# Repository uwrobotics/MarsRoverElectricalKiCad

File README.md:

# Welcome Onboard

## New Project

### Getting started

### Active Project Lists

## Onboarding

### Getting Started

Please follow the following step to create a project from template, step by step and complete the project

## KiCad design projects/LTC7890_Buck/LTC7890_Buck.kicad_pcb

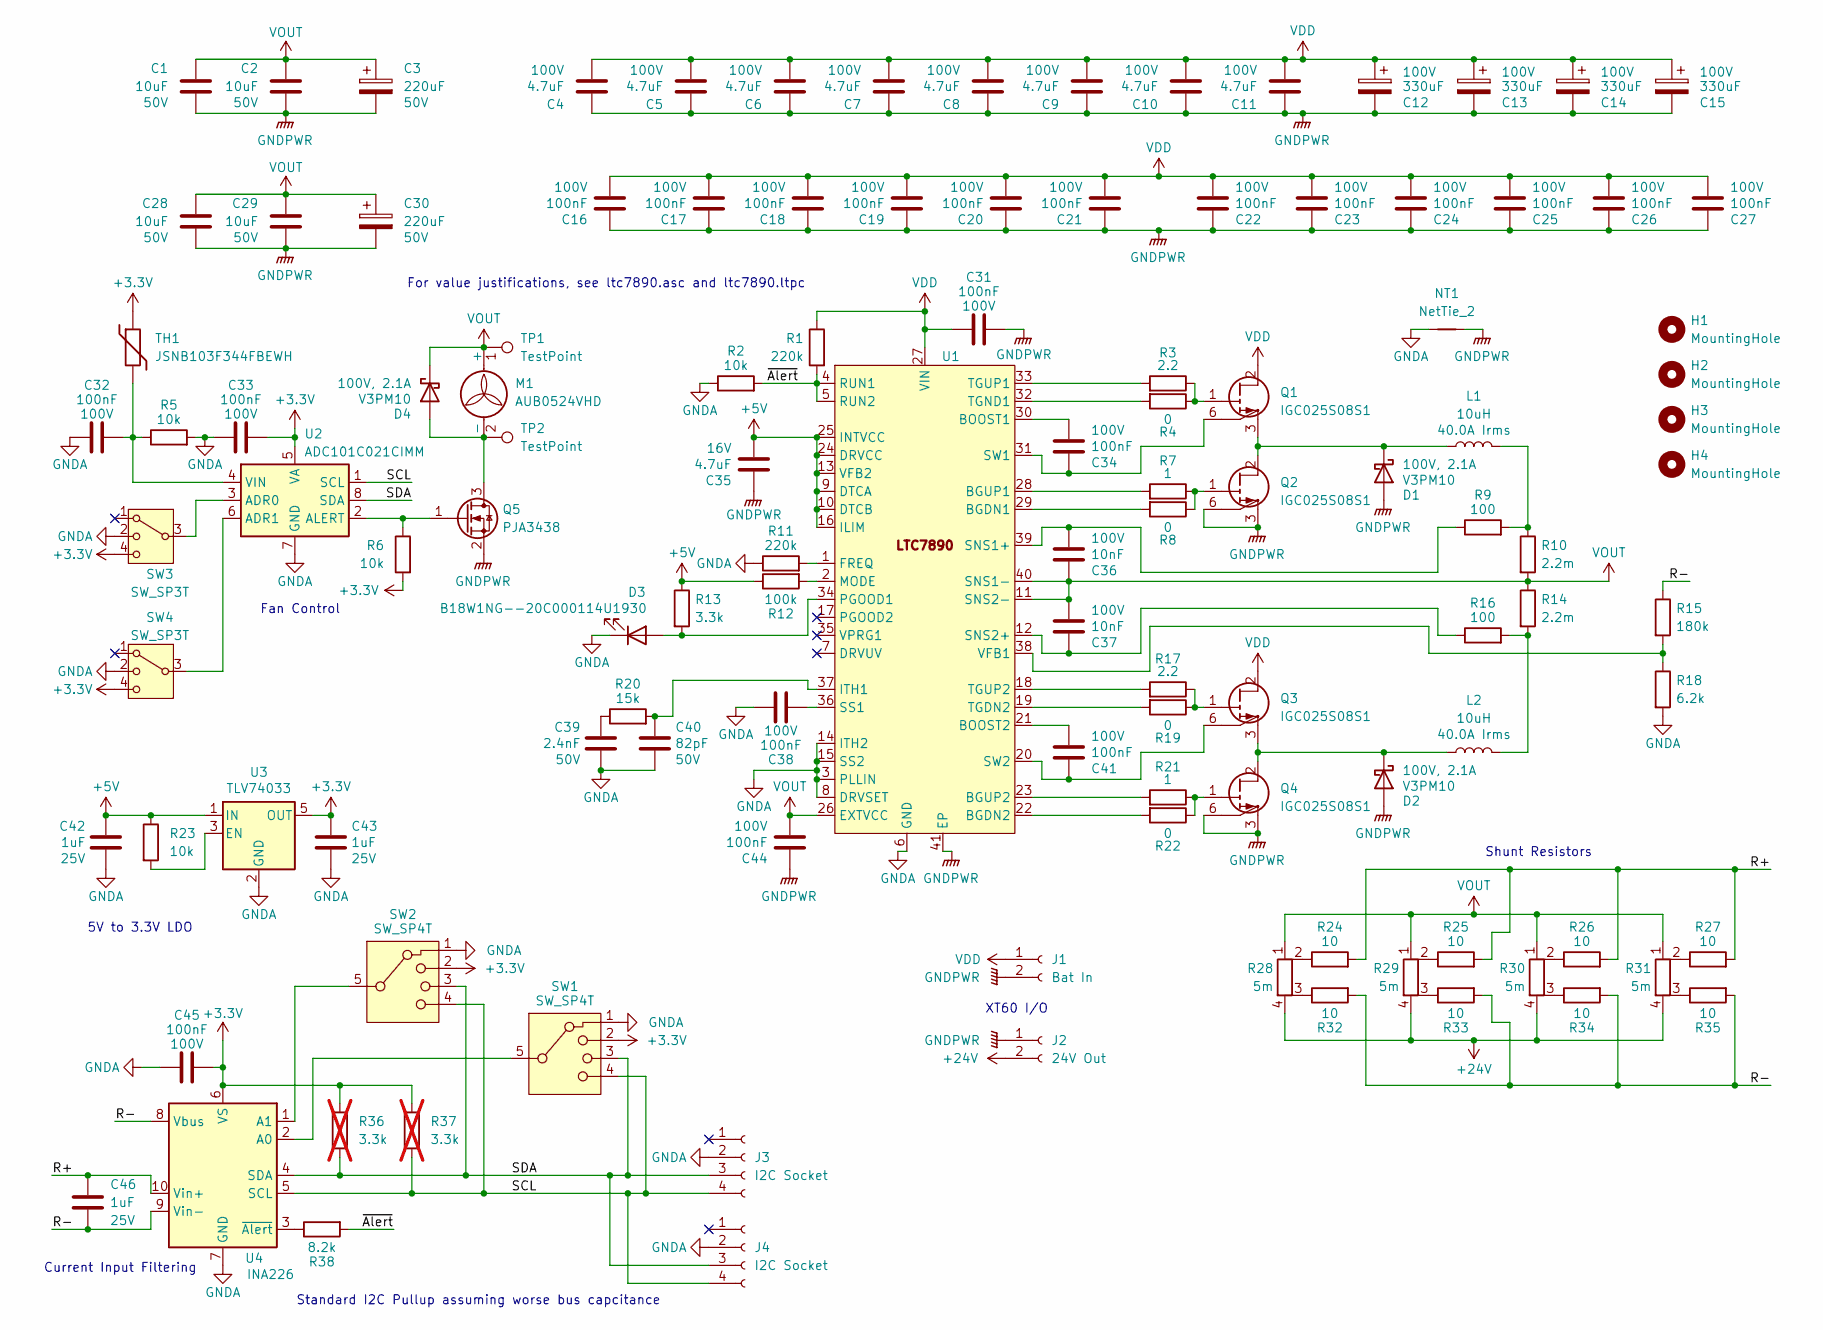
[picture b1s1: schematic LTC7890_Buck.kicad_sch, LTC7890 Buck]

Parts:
C1, C2, C28, C29: 10uF; C_1210_3225Metric; Voltage 50V
C3, C30: 220uF; CP_Radial_D10.0mm_P5.00mm; Voltage 50V
C4, C5, C6, C7, C8, C9, C10, C11: 4.7uF; C_1210_3225Metric; Voltage 100V
C12, C13, C14, C15: 330uF; CP_Radial_D12.5mm_P5.00mm; Voltage 100V
C16, C17, C18, C19, C20, C21, C22, C23, C24, C25, C26, C27, C31, C32, C33, C34, C38, C41, C44, C45: 100nF; C_0603_1608Metric; Voltage 100V
C35: 4.7uF; C_0603_1608Metric; Voltage 16V
C36, C37: 10nF; C_0603_1608Metric; Voltage 100V
C39: 2.4nF; C_0603_1608Metric; Voltage 50V
C40: 82pF; C_0603_1608Metric; Voltage 50V
C42, C43, C46: 1uF; C_0603_1608Metric; Voltage 25V
D1, D2, D4: V3PM10; D_SMP_DO-220AA; Voltage 100V, 2.1A
D3: B18W1NG--20C000114U1930; LED_0603_1608Metric
H1, H2, H3, H4: MountingHole; MountingHole_3.2mm_M3
J1: Bat In; XT60PW
J2: 24V Out; XT60PW
J3, J4: I2C Socket; JST_GH_SM04B-GHS-TB_1x04-1MP_P1.25mm_Horizontal
L1, L2: 10uH; CPQ2620H
M1: AUB0524VHD
NT1: NetTie_2; NetTie-2_SMD_Pad0.25mm
Q1, Q2, Q3, Q4: IGC025S08S1; PG-TSON-6
Q5: PJA3438; SOT-23
R1, R11: 220k; R_0603_1608Metric
R2, R5, R6, R23: 10k; R_0603_1608Metric
R3, R17: 2.2; R_0603_1608Metric
R4, R8, R19, R22: 0; R_0603_1608Metric
R7, R21: 1; R_0603_1608Metric
R9, R16: 100; R_0603_1608Metric
R10, R14: 2.2m; ASR2512
R12: 100k; R_0603_1608Metric
R13: 3.3k; R_0603_1608Metric
R15: 180k; R_0603_1608Metric
R18: 6.2k; R_0603_1608Metric
R20: 15k; R_0603_1608Metric
R24, R25, R26, R27, R32, R33, R34, R35: 10; R_0603_1608Metric
R28, R29, R30, R31: 5m; PCSR2512
R36, R37: 3.3k; R_0603_1608Metric; not fitted
R38: 8.2k; R_0603_1608Metric
SW1, SW2: SW_SP4T; SLW-1478144-5A-S-D
SW3, SW4: SW_SP3T; CL-SB-13A
TH1: JSNB103F344FBEWH; R_0603_1608Metric
TP1, TP2: TestPoint; TestPoint_THTPad_D2.0mm_Drill1.0mm
U1: LTC7890; HVQFN-40-1EP_6x6mm_P0.5mm_EP4.1x4.1mm_ThermalVias
U2: ADC101C021CIMM; MSOP-8_3x3mm_P0.65mm
U3: TLV74033; SOT-23-5
U4: INA226; TSSOP-10_3x3mm_P0.5mm

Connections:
+3.3V: C33.2, C43.1, C45.2, R6.2, R36.1, R37.1, SW1.2, SW2.2, SW3.4, SW4.4, TH1.1, U2.5 (VA), U3.5 (OUT), U4.6 (VS)
+5V: C35.2, C42.1, R12.1, R13.1, R23.1, U1.9 (DTCA), U1.10 (DTCB), U1.13 (VFB2), U1.16 (ILIM), U1.24 (DRVCC), U1.25 (INTVCC), U3.1 (IN)
+24V: J2.2, R28.4, R29.4, R30.4, R31.4
/R+: C46.1, R24.2, R25.2, R26.2, R27.2, U4.10 (Vin+)
/R-: C46.2, R15.1, R32.2, R33.2, R34.2, R35.2, U4.8 (Vbus), U4.9 (Vin-)
/SCL: J3.4, J4.4, R37.2, SW1.4, SW2.4, U2.1 (SCL), U4.5 (SCL)
/SDA: J3.3, J4.3, R36.2, SW1.3, SW2.3, U2.8 (SDA), U4.4 (SDA)
/~Alert: R1.2, R2.2, R38.2, U1.4 (RUN1), U1.5 (RUN2)
GNDA: C32.1, C33.1, C38.1, C39.2, C40.2, C42.2, C43.2, C45.1, D3.1 (K), J3.2, J4.2, NT1.1, R2.1, R5.2, R11.1, R18.2, SW1.1, SW2.1, SW3.2, SW4.2, U1.3 (PLLIN), U1.6 (GND), U1.8 (DRVSET), U1.14 (ITH2), U1.15 (SS2), U2.7 (GND), U3.2 (GND), U4.7 (GND)
GNDPWR: C1.2, C2.2, C3.2, C4.1, C5.1, C6.1, C7.1, C8.1, C9.1, C10.1, C11.1, C12.2, C13.2, C14.2, C15.2, C16.1, C17.1, C18.1, C19.1, C20.1, C21.1, C22.1, C23.1, C24.1, C25.1, C26.1, C27.1, C28.2, C29.2, C30.2, C31.2, C35.1, C44.1, D1.2 (A), D2.2 (A), J1.2, J2.1, NT1.2, Q2.3 (S), Q2.5 (S), Q2.6 (SS), Q4.3 (S), Q4.5 (S), Q4.6 (SS), Q5.2 (S), U1.41 (EP)
unnamed: C39.1, R20.1
unnamed: D1.1 (K), L1.1, Q1.3 (S), Q1.5 (S), Q2.2 (D), Q2.4 (D)
unnamed: D2.1 (K), L2.2, Q3.3 (S), Q3.5 (S), Q4.2 (D), Q4.4 (D)
unnamed: D3.2 (A), R13.2, U1.34 (PGOOD1)
unnamed: D4.2 (A), M1.2 (-), Q5.3 (D), TP2.1 (1_1)
unnamed: L1.2, R9.2, R10.1
unnamed: L2.1, R14.2, R16.2
unnamed: Q1.1 (G), R3.1, R4.1
unnamed: C34.1, Q1.6 (SS), U1.31 (SW1)
unnamed: Q2.1 (G), R7.1, R8.1
unnamed: Q3.1 (G), R17.1, R19.1
unnamed: C41.1, Q3.6 (SS), U1.20 (SW2)
unnamed: Q4.1 (G), R21.1, R22.1
unnamed: Q5.1 (G), R6.1, U2.2 (ALERT)
unnamed: R24.1, R28.2
unnamed: R25.1, R29.2
unnamed: R26.1, R30.2
unnamed: R27.1, R31.2
unnamed: R28.3, R32.1
unnamed: R29.3, R33.1
unnamed: R30.3, R34.1
unnamed: R31.3, R35.1
unnamed: R8.2, U1.29 (BGDN1)
unnamed: R22.2, U1.22 (BGDN2)
unnamed: R7.2, U1.28 (BGUP1)
unnamed: R21.2, U1.23 (BGUP2)
unnamed: C34.2, U1.30 (BOOST1)
unnamed: C41.2, U1.21 (BOOST2)
unnamed: R11.2, U1.1 (FREQ)
unnamed: C40.1, R20.2, U1.37 (ITH1)
unnamed: R12.2, U1.2 (MODE)
unnamed: C36.2, R9.1, U1.39 (SNS1+)
unnamed: C37.1, R16.1, U1.12 (SNS2+)
unnamed: C38.2, U1.36 (SS1)
unnamed: R19.2, U1.19 (TGDN2)
unnamed: R4.2, U1.32 (TGND1)
unnamed: R3.2, U1.33 (TGUP1)
unnamed: R17.2, U1.18 (TGUP2)
unnamed: R15.2, R18.1, U1.38 (VFB1)
unnamed: SW3.3, U2.3 (ADR0)
unnamed: SW4.3, U2.6 (ADR1)
unnamed: C32.2, R5.1, TH1.2, U2.4 (VIN)
unnamed: R23.2, U3.3 (EN)
unnamed: SW1.5, U4.2 (A0)
unnamed: SW2.5, U4.1 (A1)
unnamed: R38.1, U4.3 (~Alert)
VDD: C4.2, C5.2, C6.2, C7.2, C8.2, C9.2, C10.2, C11.2, C12.1, C13.1, C14.1, C15.1, C16.2, C17.2, C18.2, C19.2, C20.2, C21.2, C22.2, C23.2, C24.2, C25.2, C26.2, C27.2, C31.1, J1.1, J3.MP, J4.MP, Q1.2 (D), Q1.4 (D), Q3.2 (D), Q3.4 (D), R1.1, U1.27 (VIN)
VOUT: C1.1, C2.1, C3.1, C28.1, C29.1, C30.1, C36.1, C37.2, C44.2, D4.1 (K), M1.1 (+), R10.2, R14.1, R28.1, R29.1, R30.1, R31.1, TP1.1 (1_1), U1.11 (SNS2-), U1.26 (EXTVCC), U1.40 (SNS1-)

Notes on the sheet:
Fan Control
XT60 I/O
For value justifications, see ltc7890.asc and ltc7890.ltpc
5V to 3.3V LDO
Current Input Filtering
Shunt Resistors
Standard I2C Pullup assuming worse bus capcitance

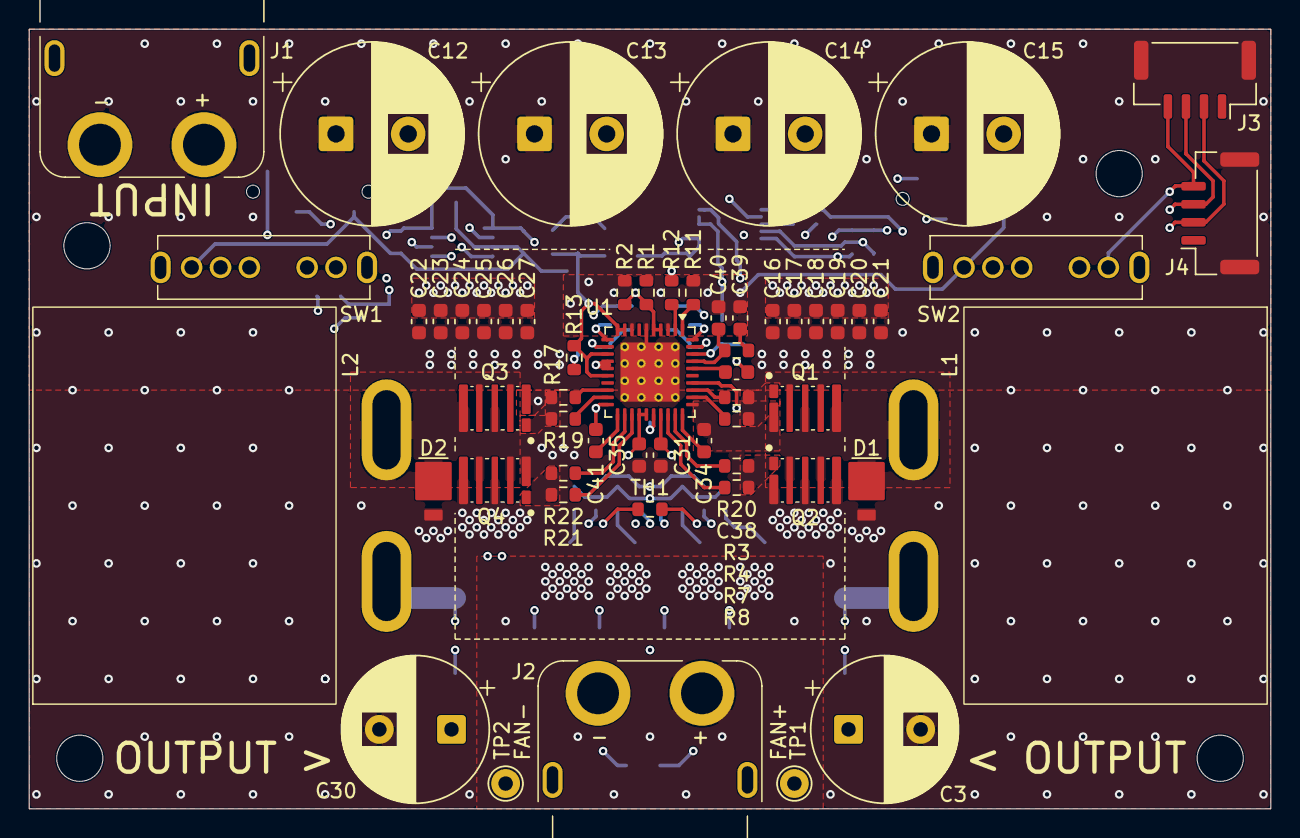
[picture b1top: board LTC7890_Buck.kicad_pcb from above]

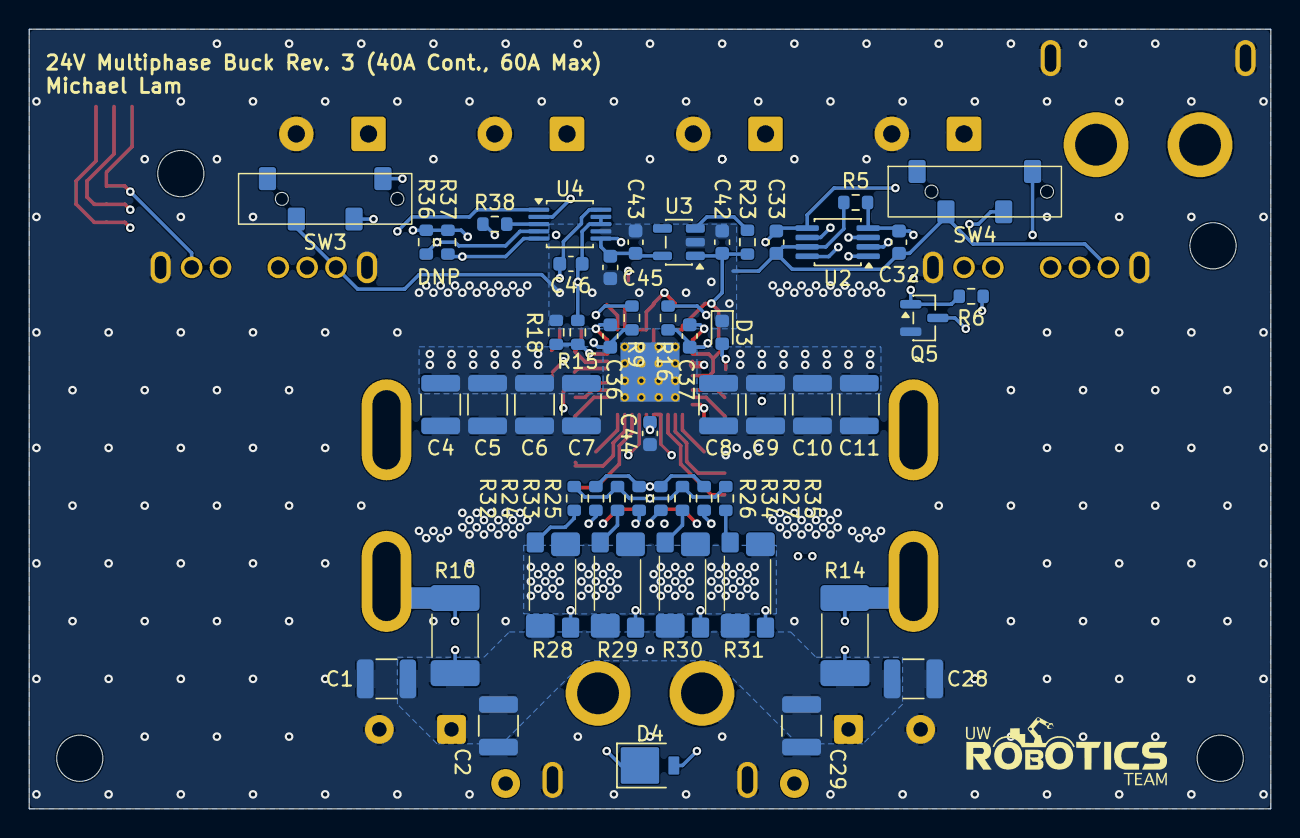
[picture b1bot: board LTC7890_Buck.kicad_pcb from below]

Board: 4 copper layers, 86.0 x 54.0 mm, 115 parts (53 on the bottom side), 58 nets.

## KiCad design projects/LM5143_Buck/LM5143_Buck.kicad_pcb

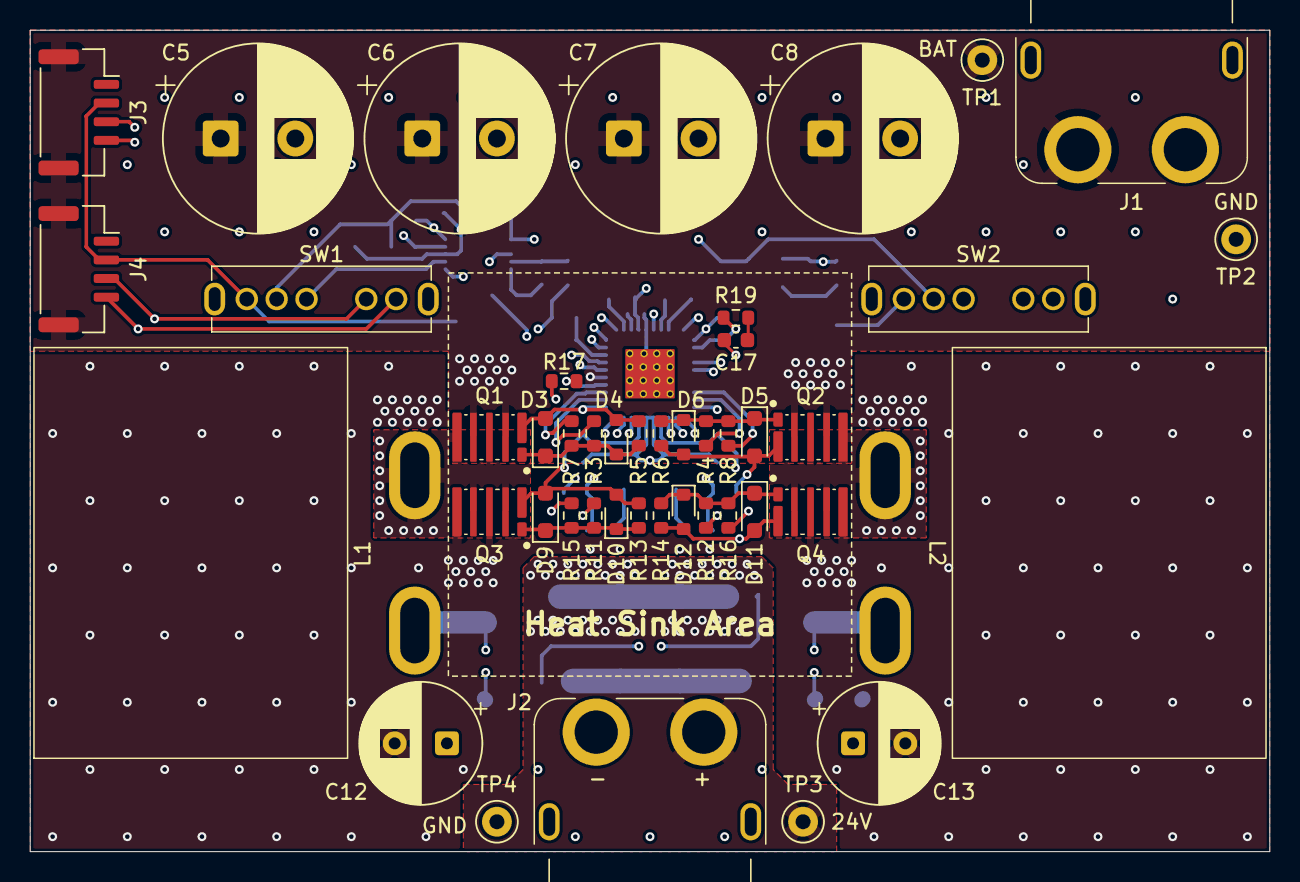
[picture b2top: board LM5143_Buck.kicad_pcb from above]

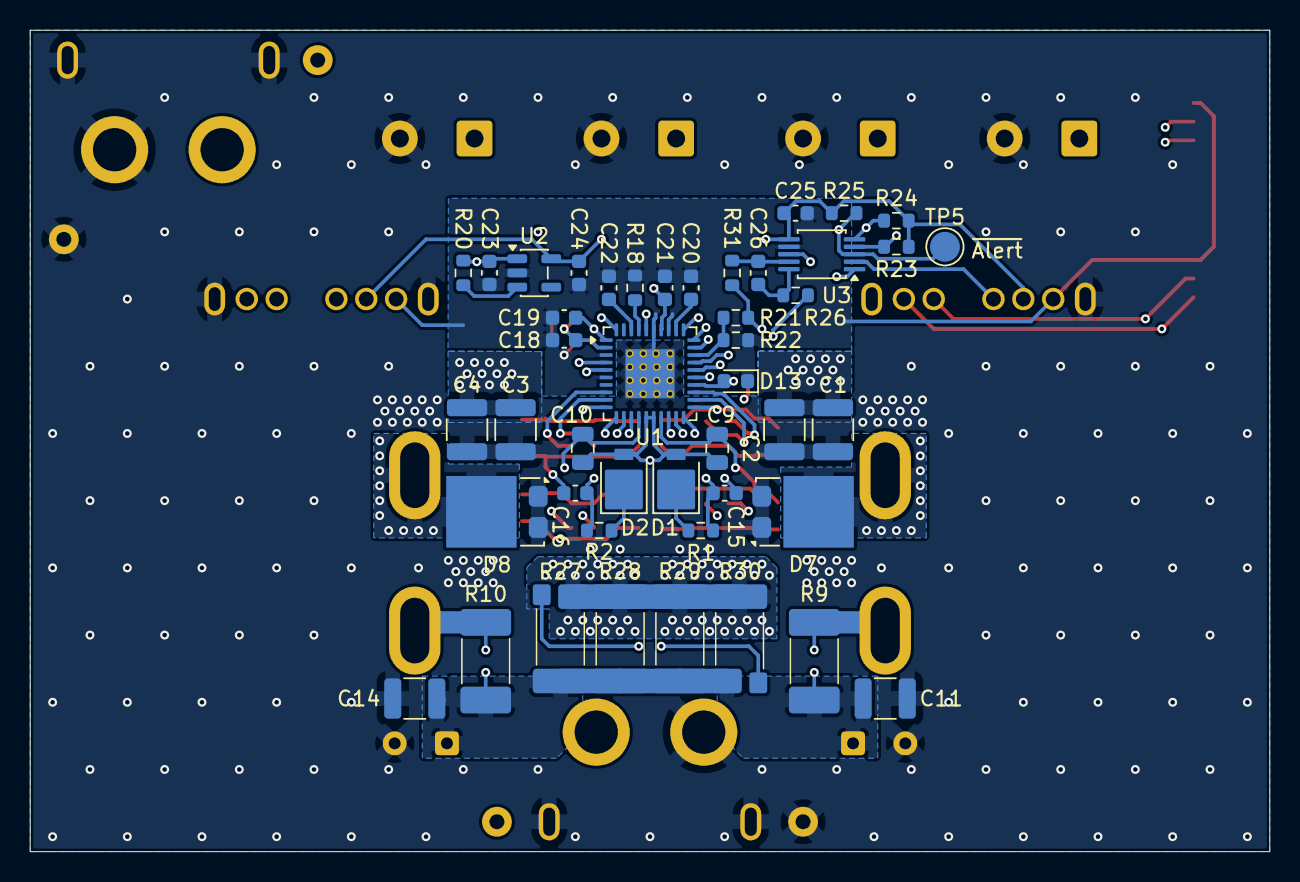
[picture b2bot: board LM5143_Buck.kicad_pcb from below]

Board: 4 copper layers, 83.0 x 55.0 mm, 91 parts (46 on the bottom side), 48 nets.

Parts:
C1, C2, C3, C4: 4.7uF; C_1210_3225Metric
C5, C6, C7, C8: 330uF; CP_Radial_D12.5mm_P5.00mm
C9, C10: 2.2uF; C_0805_2012Metric
C11, C14: 10uF; C_1210_3225Metric
C12, C13: 100uF; CP_Radial_D8.0mm_P3.50mm
C15, C16, C19, C25: 100nF; C_0603_1608Metric
C17: 3.3nF; C_0603_1608Metric
C18: 82pF; C_0603_1608Metric
C20, C21: 470nF; C_0603_1608Metric
C22: 10nF; C_0603_1608Metric
C23, C24, C26: 1uF; C_0603_1608Metric
D1, D2: V2PM10L; D_SMP_DO-220AA
D3, D5, D9, D11: CUS10S30; D_SOD-323_HandSoldering
D4, D6, D10, D12: PLZ5V1C; D_MicroSMF
D7, D8: MBR15H120PC-AU; TO-277A
D13: B18W1NG--20C000114U1930; LED_0603_1608Metric
J1: Bat In; XT60PW
J2: 24V Out; XT60PW
J3, J4: I2C Socket; JST_GH_SM04B-GHS-TB_1x04-1MP_P1.25mm_Horizontal
L1, L2: 10uH; ER26A
NT1: NetTie_2; NetTie-2_SMD_Pad0.25mm
Q1, Q2, Q3, Q4: IGC025S08S1; PG‑TSON‑6
R1, R2: 2.2; R_0603_1608Metric
R3, R4, R11, R12: 3.3; R_0603_1608Metric
R5, R6, R13, R14, R20, R22: 10k; R_0603_1608Metric
R7, R8, R15, R16: 1; R_0603_1608Metric
R9, R10: 2.2m; ASR2512
R17, R23, R24, R25: 3.3k; R_0603_1608Metric
R18: 100k; R_0603_1608Metric
R19: 18k; R_0603_1608Metric
R21: 390k; R_0603_1608Metric
R26, R31: 10; R_0603_1608Metric
R27, R30: 5m; PCSR2512_Alt
R28, R29: 5m; PCSR2512_Alt_2
SW1, SW2: Addr_Switch; SLW-1478144-5A-S-D
TP1, TP2, TP3, TP4: TestPoint; TestPoint_Keystone_5000-5004_Miniature
TP5: TestPoint; TestPoint_Pad_D2.0mm
U1: Texas_VQFN-40-1EP_6x6mm_P0.5mm_EP3.3x3.3mm_ThermalVias
U2: TLV74033; SOT-23-5
U3: INA226; VSSOP-10_3x3mm_P0.5mm

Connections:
+3.3V: C24.1, C25.2, R23.1, R24.1, R25.1, SW1.2, SW2.2, U2.5 (OUT), U3.6 (VS)
+5V: C9.1, C10.1, C23.1, D1.2 (A), D2.2 (A), R17.1, R20.1, U1.15 (VCC), U1.16 (VCC), U2.1 (IN)
+24V: J2.2, R21.2, R27.1, R28.2, R29.2, R30.2, R31.1, TP3.1, U3.8 (Vbus)
/FB1: R21.1, R22.2, U1.28 (FB1)
/~Alert: R25.2, TP5.1, U1.31 (EN1), U1.40 (EN2), U3.3 (~Alert)
GNDA: C17.1, C18.1, C19.2, C20.2, C21.2, C22.2, C23.2, C24.2, C25.1, D13.1 (K), J3.2, J4.2, NT1.1, R18.1, R22.1, SW1.1, SW2.1, U1.3 (FB2), U1.6 (VCCX), U1.33 (DEMB), U1.35 (AGND), U2.2 (GND), U3.7 (GND)
GNDPWR: C1.1, C2.1, C3.1, C4.1, C5.2, C6.2, C7.2, C8.2, C11.2, C12.2, C13.2, C14.2, D7.1 (A), D7.2 (A), D8.1 (A), D8.2 (A), J1.1, J2.1, NT1.2, Q3.3 (S), Q3.5 (S), Q4.3 (S), Q4.5 (S), TP2.1, TP4.1, U1.41 (EP)
unnamed: C17.2, R19.1
unnamed: D1.1 (K), R1.1
unnamed: D2.1 (K), R2.1
unnamed: C15.1, D3.2 (A), D4.2 (A), Q1.6 (DS), R5.2, U1.21 (SW1)
unnamed: D3.1 (K), D4.1 (K), Q1.1 (G), R3.1, R5.1, R7.1
unnamed: C16.1, D5.2 (A), D6.2 (A), Q2.6 (DS), R6.2, U1.10 (SW2)
unnamed: D5.1 (K), D6.1 (K), Q2.1 (G), R4.1, R6.1, R8.1
unnamed: D7.3 (K), L1.2, Q1.3 (S), Q1.5 (S), Q3.2 (D), Q3.4 (D)
unnamed: D8.3 (K), L2.1, Q2.3 (S), Q2.5 (S), Q4.2 (D), Q4.4 (D)
unnamed: D9.1 (K), D10.1 (K), Q3.1 (G), R11.1, R13.1, R15.1
unnamed: D11.1 (K), D12.1 (K), Q4.1 (G), R12.1, R14.1, R16.1
unnamed: D13.2 (A), R17.2, U1.24 (PG1)
unnamed: J3.3, J4.3, R23.2, SW1.3, SW2.3, U3.4 (SDA)
unnamed: J3.4, J4.4, R24.2, SW1.4, SW2.4, U3.5 (SCL)
unnamed: C18.2, R19.2, U1.2 (COMP2), U1.29 (COMP1)
unnamed: L1.1, R9.1, U1.27 (CS1)
unnamed: L2.2, R10.1, U1.4 (CS2)
unnamed: C22.1, U1.38 (DITH)
unnamed: C15.2, R1.2, U1.20 (HB1)
unnamed: C16.2, R2.2, U1.11 (HB2)
unnamed: R3.2, U1.22 (HO1)
unnamed: R4.2, U1.9 (HO2)
unnamed: R7.2, U1.23 (HOL1)
unnamed: R8.2, U1.8 (HOL2)
unnamed: R11.2, U1.18 (LO1)
unnamed: R12.2, U1.13 (LO2)
unnamed: R15.2, U1.19 (LOL1)
unnamed: R16.2, U1.12 (LOL2)
unnamed: C20.1, U1.32 (RES)
unnamed: R18.2, U1.37 (RT)
unnamed: C19.1, U1.1 (SS2), U1.30 (SS1)
unnamed: R20.2, U2.3 (EN)
unnamed: SW1.5, U3.2 (A0)
unnamed: SW2.5, U3.1 (A1)
unnamed: C26.1, R26.2, U3.10 (Vin+)
unnamed: C26.2, R31.2, U3.9 (Vin-)
PGND1: C9.2, D9.2 (A), D10.2 (A), Q3.6 (DS), R13.2, U1.17 (PGND1)
PGND2: C10.2, D11.2 (A), D12.2 (A), Q4.6 (DS), R14.2, U1.14 (PGND2)
VDD: C1.2, C2.2, C3.2, C4.2, C5.1, C6.1, C7.1, C8.1, J1.2, J3.MP, J4.MP, Q1.2 (D), Q1.4 (D), Q2.2 (D), Q2.4 (D), TP1.1, U1.25 (VIN)
VDDA: C21.1, U1.34 (MODE), U1.36 (VDDA)
VOUT: C11.1, C12.1, C13.1, C14.1, R9.2, R10.2, R26.1, R27.2, R28.1, R29.1, R30.1, U1.5 (VOUT2), U1.26 (VOUT1)

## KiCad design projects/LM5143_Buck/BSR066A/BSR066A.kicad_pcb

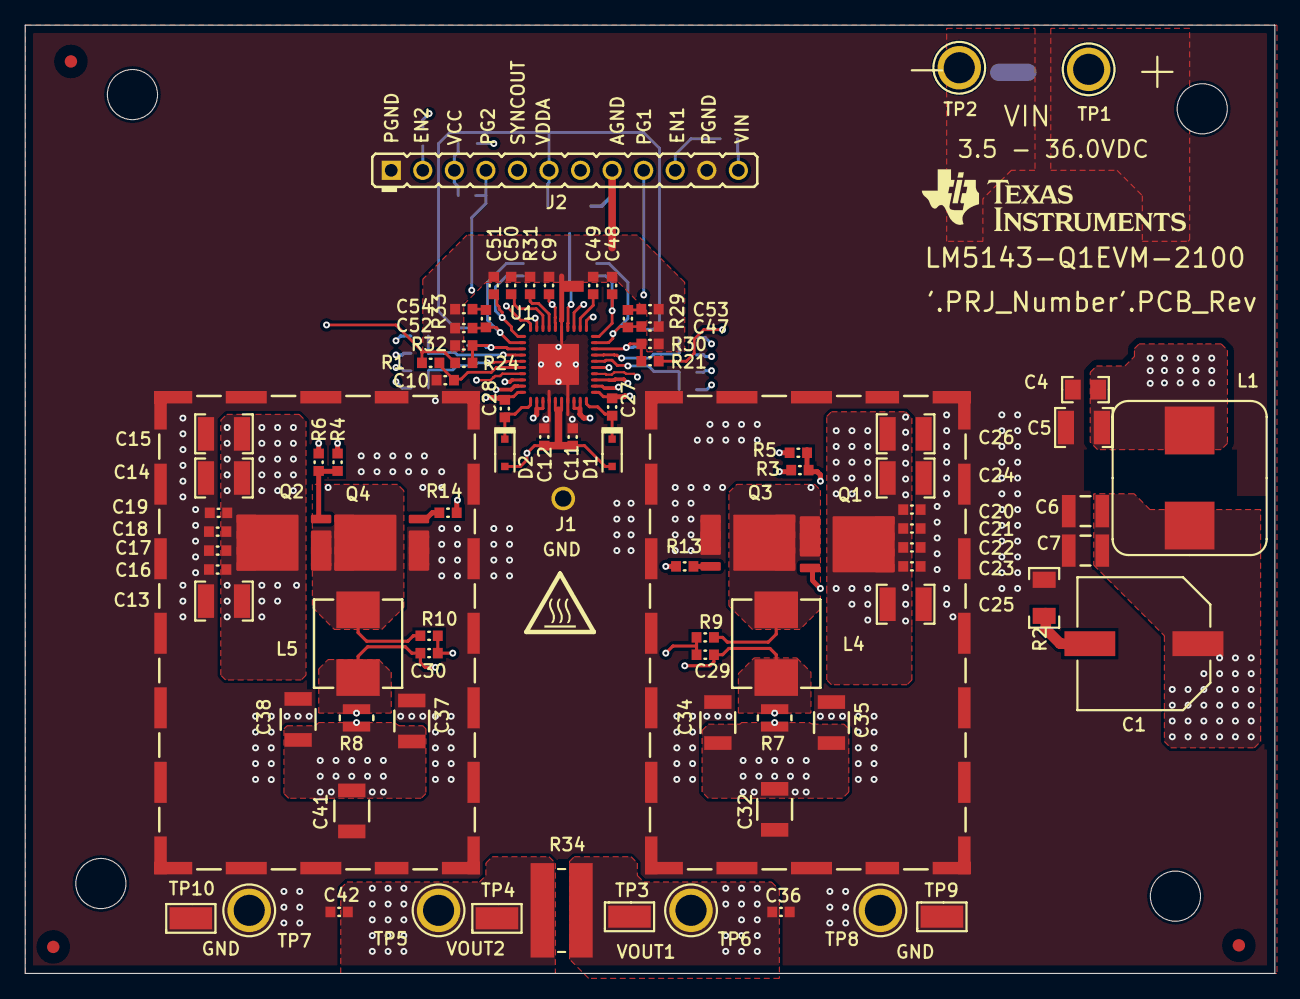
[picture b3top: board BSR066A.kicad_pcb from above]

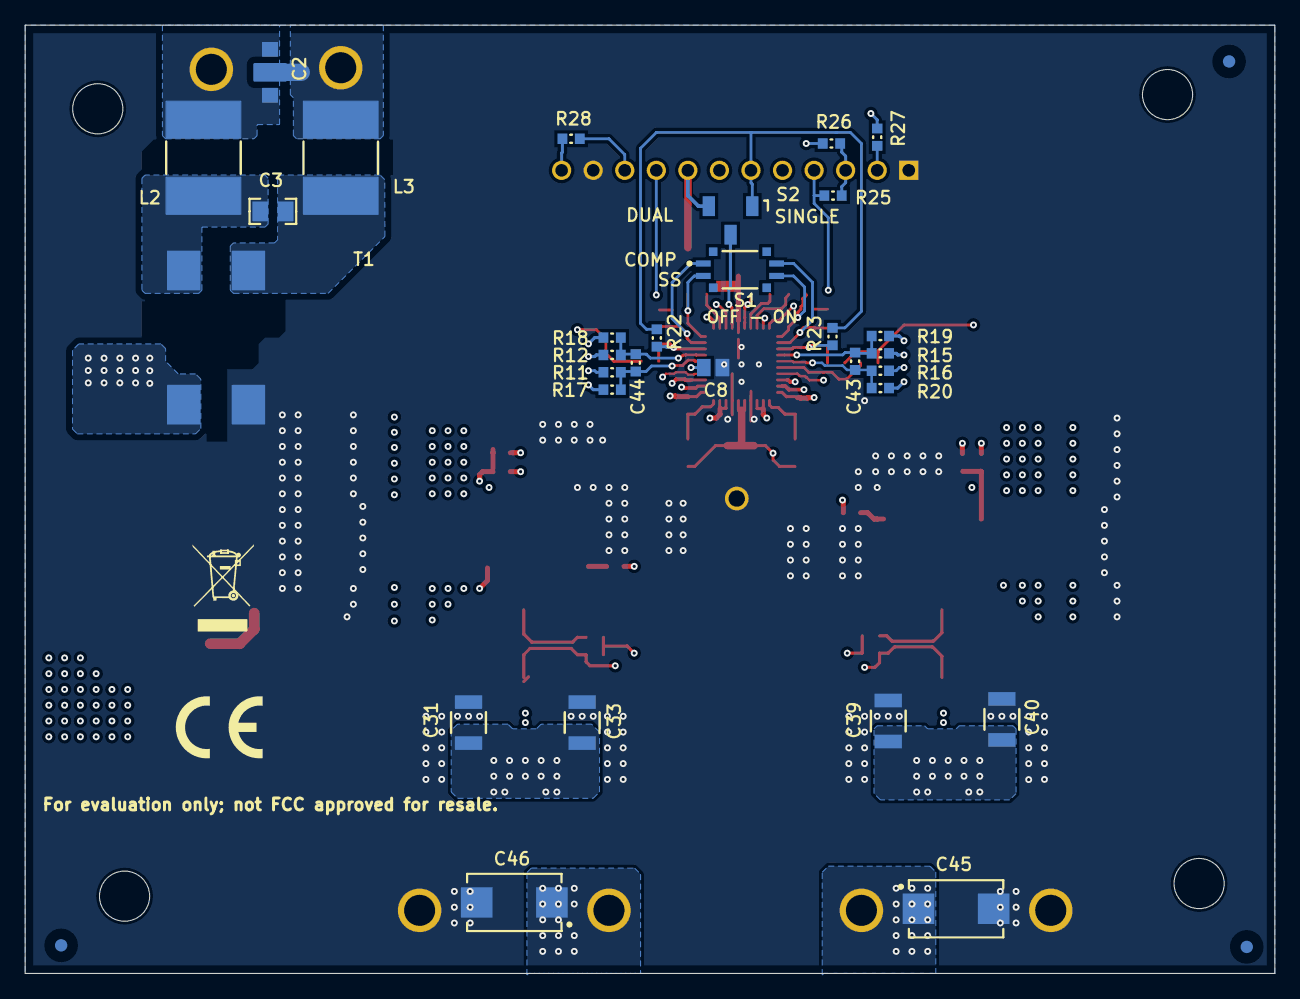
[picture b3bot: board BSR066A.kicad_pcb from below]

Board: 6 copper layers, 100.6 x 76.3 mm, 144 parts (40 on the bottom side), 54 nets.

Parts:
C1: EEE-FC1H470P; SM_RADIAL_G
C2: 1uF; YFF31AH2A10xM
C3, C4: C0805C104K1RACTU; 0805_HV
C5, C13, C14, C15, C24, C25, C26: UMJ325KB7106KMHT; 1210_270
C6, C7: UMJ325KB7106KMHT; 1210_270L
C8: GRM21BR72A474KA73L; 0805L
C9: GCM188R71C474KA55D; 0603L
C10, C11, C12: GRM188R71A225KE15D; 0603L
C16, C17, C18, C19, C20, C21, C22, C23, C50: GRM188R72A103KA01D; 0603L
C27, C28, C29, C30, C42, C48, C51: CGA3E2X7R1E104K080AA; 0603L
C31, C32, C33, C34, C35, C37, C38, C39, C40, C41: CGA6P1X7S0J476M250AC; 1210_280
C36: GRM188R72A104KA35D; 0603L
C43, C44: 06031A330JAT2A; 0603L
C45, C46: T598D227M010ATE025; 7343-31
C47, C52: GRM1885C1H150JA01D; 0603L
C49: CL10B224KO8VPNC; 0603L
C53, C54: C0603C102K5HACTU; 0603L
D1, D2: 60V; SOD-323F
FID1, FID2, FID3, FID4, FID5, FID6: Fiducial; Fiducial10-20
H1, H2: BMI-S-205-F; Laird_BMI-S-205-F
H3, H4, H5, H6: 1902C; Keystone_1902C
J1: 1040; CONN_1040
J2: PBC12SABN; Sullins_PxC12SABN
L1: 744325420; WE-HC6
L2, L3: 800 ohm; 2220_390
L4, L5: 744373460068; WE-LHMI_7030
LOGO2: CAUTION HOT SURFACE; IEC_HotSurface_Small
Logo1: CE Mark; CE_Mark_5mm
Logo3: Texas Instruments; TI_Stacked_Overlay_Small
Logo4: FCC disclaimer; FCC_disclaimer
Logo5: WEEE logo; WEEE_Minimum
MH1, MH2, MH3, MH4: MTG_NoPads; MTG_159mil
NT1: Net-Tie; Net-Tie_10mil
Q1, Q2, Q3, Q4: IPC50N04S5L5R5ATMA1; PG-TDSON-8-33
R1: RC0603FR-071RL; 0603L
R2: CRCW12061R00JNEA; 1206
R3, R4, R5, R6, R11, R13, R14, R16, R22, R23: CRCW06030000Z0EA; 0603L
R7, R8: KRL2012M-R007-F-T1; KRL2012
R9, R10: CRCW06031K50FKEA; 0603L
R12, R15: CRCW060349R9FKEA; 0603L
R17, R18, R19, R20: CRCW0603100RFKEA; 0603L
R21, R24, R25, R26, R27, R28: CRCW0603100KFKEA; 0603L
R29: CRCW060320K0FKEA; 0603L
R30: CRCW060322K1FKEA; 0603L
R31: RC0603FR-0710KL; 0603L
R32: CRCW060313K7FKEA; 0603L
R33: CRCW060324K9FKEA; 0603L
R34: RCL12250000Z0EG; 2512_WIDE_VISHAY
S1: CVS-02TB; SW_CVS-02B
S2: CJS-1201TA; SW_CJS_1201A
T1: ACM12V-701-2PL-TL00; TDK_ACM12V
TP1, TP2, TP5, TP6, TP7, TP8: 1598-2; Keystone1598-2
TP3, TP4, TP9, TP10: 5015; Testpoint_Keystone_Miniature
U1: LM5143QRWGRQ1; RWG0040A
ZZ1: These assemblies are ESD sensitive, ESD precautio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; AssemblyNote
ZZ2: These assemblies must be clean and free from flux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; AssemblyNote
ZZ3: These assemblies must comply with workmanship sta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; AssemblyNote
ZZ4: After final wash remove kapton tape cover from SW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; AssemblyNote
ZZ5: Set SW1 A & B to OFF position; AssemblyNote
ZZ6: Set SW2 to SINGLE position; AssemblyNote
ZZ7: Place Shunt Jumper SH-J1 onto J2 onto pins 6-7 (V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; AssemblyNote

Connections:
AGND: C9.1, C47.2, C48.2, C49.2, C50.2, C51.2, C52.2, C53.2, C54.2, J2.8, NT1.1, R30.1, R31.1, R32.1, S2.3, U1.35
COMP1: C47.1, R29.2, S1.1, U1.29
COMP2: C52.1, R33.2, S1.4, U1.2
DEMB: J2.7, U1.33
EN1: J2.10, R28.1, U1.31
EN2: J2.2, R27.1, U1.40
FB1: R21.1, R22.1, R30.2, U1.28
FB2: R23.1, R24.1, R32.2, U1.3
NetC1_2: C1.2, R2.2
NetC2_1: C2.1, C2.2, L2.1, TP1.1
NetC2_3: C2.3, L3.1, TP2.1
NetC3_1: C3.1, L3.2, T1.1
NetC3_2: C3.2, L2.2, T1.2
NetC4_1: C4.1, C5.1, L1.1, T1.3
NetC10_1: C10.1, R1.1, U1.6
NetC27_1: C27.1, L4.1, Q1.1, Q1.2, Q1.3, Q3.5, Q3.6, Q3.7, Q3.8, R9.2, U1.21
NetC27_2: C27.2, D1.1, U1.20
NetC28_1: C28.1, L5.1, Q2.1, Q2.2, Q2.3, Q4.5, Q4.6, Q4.7, Q4.8, R10.2, U1.10
NetC28_2: C28.2, D2.1, U1.11
NetC29_1: C29.1, R9.1, R18.2
NetC29_2: C29.2, L4.2, R7.1, R12.2, R17.2
NetC30_1: C30.1, R10.1, R19.2
NetC30_2: C30.2, L5.2, R8.1, R15.2, R20.2
NetC43_1: C43.1, R16.1, R20.1, U1.5
NetC43_2: C43.2, R15.1, R19.1, U1.4
NetC44_1: C44.1, R11.1, R17.1, U1.26
NetC44_2: C44.2, R12.1, R18.1, U1.27
NetC49_1: C49.1, U1.32
NetC50_1: C50.1, U1.38
NetC53_1: C53.1, R29.1
NetC54_1: C54.1, R33.1
NetQ1_4: Q1.4, R3.2, R5.2
NetQ2_4: Q2.4, R4.2, R6.2
NetQ3_4: Q3.4, R13.2
NetQ4_4: Q4.4, R14.2
NetR3_1: R3.1, U1.22
NetR4_1: R4.1, U1.9
NetR5_1: R5.1, U1.23
NetR6_1: R6.1, U1.8
NetR13_1: R13.1, U1.18, U1.19
NetR14_1: R14.1, U1.12, U1.13
NetR31_2: R31.2, U1.37
NetS2_2: S2.2, U1.34
PG1: J2.9, R26.1, U1.24
PG2: J2.4, R25.1, U1.7
PGND: C4.2, C5.2, C6.2, C7.2, C8.1, C10.2, C11.2, C12.2, C13.2, C14.2, C15.2, C16.1, C17.1, C18.1, C19.1, C20.1, C21.1, C22.1, C23.1, C24.2, C25.2, C26.2, C31.2, C32.2, C33.2, C34.2, C35.2, C36.2, C37.2, C38.2, C39.2, C40.2, C41.2, C42.2, C45.2, C46.2, H1.1, H2.1, J1.1, J2.1, J2.11, NT1.2, Q3.1, Q3.2, Q3.3, Q4.1, Q4.2, Q4.3, R2.1, T1.4, TP7.1, TP8.1, TP9.1, TP10.1, U1.14, U1.17, U1.41
SS1: C48.1, S1.2, U1.30
SS2: C51.1, S1.3, U1.1
SYNCOUT: J2.5, U1.39
VCC: C11.1, C12.1, D1.2, D2.2, J2.3, R25.2, R26.2, U1.15, U1.16
VDDA: C9.2, J2.6, R22.2, R23.2, S2.1, U1.36
VIN: C1.1, C6.1, C7.1, C8.2, C13.1, C14.1, C15.1, C16.2, C17.2, C18.2, C19.2, C20.2, C21.2, C22.2, C23.2, C24.1, C25.1, C26.1, J2.12, L1.2, Q1.5, Q1.6, Q1.7, Q1.8, Q2.5, Q2.6, Q2.7, Q2.8, R27.2, R28.2, U1.25
VOUT1: C31.1, C32.1, C33.1, C34.1, C35.1, C36.1, C46.1, R7.2, R11.2, R21.2, R34.1, TP3.1, TP6.1
VOUT2: C37.1, C38.1, C39.1, C40.1, C41.1, C42.1, C45.1, R1.2, R8.2, R16.2, R24.2, R34.2, TP4.1, TP5.1
